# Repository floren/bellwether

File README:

# The Bellwether Mouse

This repo should contain everything you need to make a [Bellwether mouse](https://jfloren.net/bellwether.html).

## 3D-printed case

Inside the case/ subdirectory you'll find two FreeCAD files, "base" (the bottom part of the mouse) and "body" (the curved top which fits in your hand).

These should be printed in PLA. I've had good luck with my Prusa Mini. I strongly suggest using a raft when printing the body, and *not* using a raft for the base.

Check out the releases for pre-built STL files.

## PCB

The board was designed using KiCAD. If you use OSH Park, you should be able to just upload board/depraz_board.kicad_pcb directly on their site. For other PCB services, you may need to open KiCAD and export Gerber files etc.

## Circuit & BOM

You can check out the schematic in schematic.pdf

bom.csv is a circuit bill of materials. Most stuff should be available from parts companies in the US, but for the PMW3389 sensor you'll probably need to go to AliExpress (e.g. https://www.aliexpress.us/item/2251832705021246.html)

You'll also need 3 momentary pushbutton switches such as https://www.digikey.com/en/products/detail/5501M1BLKX/EG1701-ND/101654

Although you don't have to, I recommend using a DIP socket for the microcontroller in case you toast the microcontroller.

## Assembly

### Circuit assembly

In general it's all pretty straightforward but I strongly recommend installing the SMD level shifters first, all the rest of the components next, and then do the mouse sensor *last*.

### Doing the switches

I recommend gluing down the switches first. Gently pry off the button from each switch and set it aside. Then put a small dab of Gorilla Glue in the slot on the base, press the switch onto it, and make sure it's aligned straight. Use a clamp to hold the switch in place while the glue dries (I used something like https://www.amazon.com/Professional-Plastic-Backdrop-Photography-Improvement/dp/B08RXW32H4/). Once the glue is dry, make sure the switch is firmly seated and use an exacto knife to trim away any glue which oozed out, then press the button back onto the switch face.

Solder two wires onto each switch, on the normally-open pins. The wires should have Dupont pin connectors on the ends; I just took some jumper wires I had lying around (with a connector on each end) and cut them in half. See http://jfloren.net/content/bellwether/base2.jpg

### Physical assembly

You'll need the following parts to assemble the case:

* 8x M2x0.4mm heatserts: https://www.mcmaster.com/94459A120/
* 4x M2x0.4mm flathead screws (for the bottom): https://www.mcmaster.com/91294A003/
* 4x M2x0.4mm button head screws (to hold the board down): https://www.mcmaster.com/92095A451/

Additional stuff you'll want:

* A USB cable. Should be USB-A on one end, and a female pin header connector at the other. You can start with https://www.digikey.com/en/products/detail/assmann-wsw-components/A-USB20AM-OE-200BK28/10408422 and use https://www.amazon.com/Taiss-Ratcheting-Connector-Crimping-Terminal/dp/B0B11RLGDZ to crimp on a 4-pin header to the other end. You may be able to find these pre-made, e.g. https://www.amazon.com/dp/B07ZPT2NMT
* Friction tape (https://www.amazon.com/gp/product/B0000CBIAT) to wrap around the USB cable where it leaves the mouse. This appears to be what my original Depraz mouse used.
* Teflon tape to make skates for the bottom. I used https://www.amazon.com/gp/product/B01LZ44P6M and punched out pieces using https://www.amazon.com/gp/product/B00006IBK9

Use your soldering iron to install the heatserts flush in the corresponding holes of the case.

Position the lens on the bottom of the mouse sensor, then set the PCB on the 3d printed base. Use the button-head screws to hold down the PCB; don't overtighten!

Plug in the switches. Note that the headers on the board are labeled R, M, and L for right, middle, and left.

Plug the USB cable into the 4-pin USB header. Lay it across the board to where the cable hole in the case will go; mark this point and put a layer or two of friction tape on the cable there.

Gently slide the top of the case over the switches; there's a "right way" to do it, which takes a bit of gentle experimentation to find. Once you get the two pieces together, use flathead screws to hold them together.

Punch out four pieces of Teflon tape and stick them to the bottom for skates.

### Flashing the firmware

The firmware organization sucks, but I am not good enough at PIC programming to properly clean it up. PRs welcome.

Plug your PIC programmer into the PROGRAM header on the board.

Open MPLAB X IDE and load firmware/depraz/apps/usb/device/hid_mouse/firmware/low_pin_count_usb_development_kit_pic16f1459.x

I found that it worked when I set up the PICkit3 to provide power at 3.5V. Your other option is to plug in the USB cable before programming to power the device externally.

### Adding heft

You'll probably find that the mouse by itself is way too light. I hot-glued a bunch of lead fishing weights to the inside and it was much more pleasant.

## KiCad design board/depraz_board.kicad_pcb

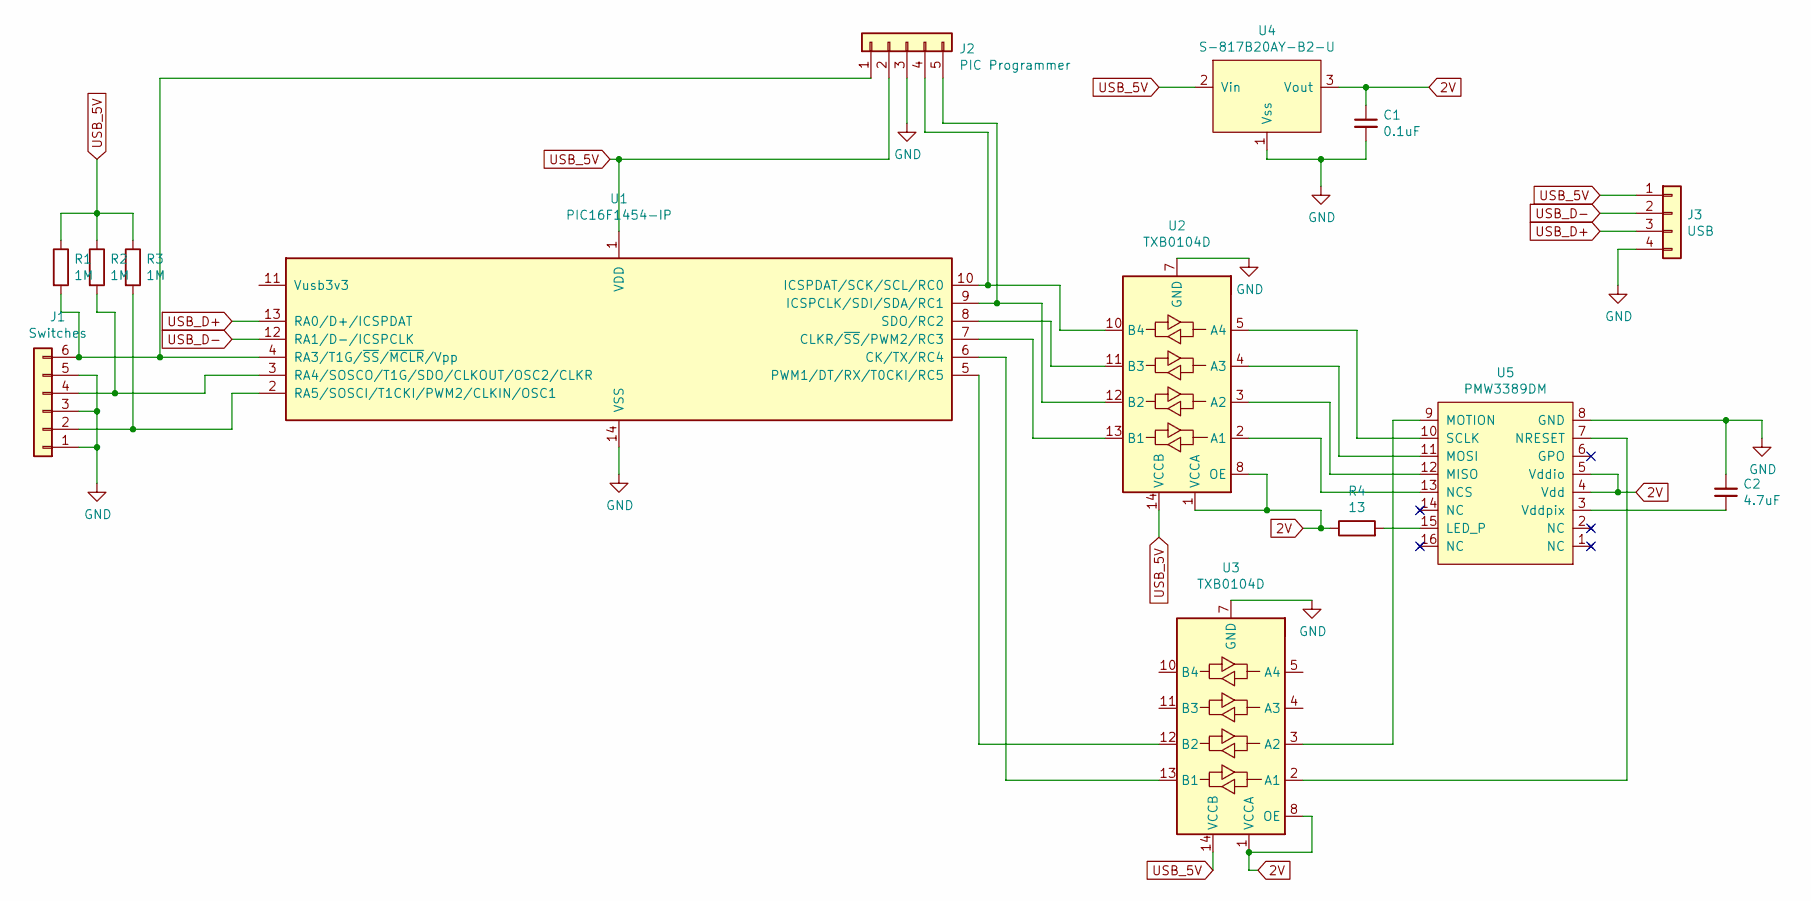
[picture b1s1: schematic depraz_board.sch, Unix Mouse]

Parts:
C1: 0.1uF; C_Disc_D8.0mm_W2.5mm_P5.00mm
C2: 4.7uF; C_Disc_D4.7mm_W2.5mm_P5.00mm
J1: Switches; PinHeader_1x06_P2.54mm_Vertical
J2: PIC Programmer; PinHeader_1x05_P2.54mm_Vertical
J3: USB; PinHeader_1x04_P2.54mm_Vertical
R1, R2, R3: 1M; R_Axial_DIN0207_L6.3mm_D2.5mm_P5.08mm_Vertical
R4: 13; R_Axial_DIN0207_L6.3mm_D2.5mm_P5.08mm_Vertical
U1: PIC16F1454-IP; DIP-14_W7.62mm
U2, U3: TXB0104D; SOIC-14_3.9x8.7mm_P1.27mm
U4: S-817B20AY-B2-U; TO-92L_Inline
U5: PMW3389DM; pmw3389

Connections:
2V: C1.1, R4.1, U2.1 (VCCA), U2.8 (OE), U3.1 (VCCA), U3.8 (OE), U4.3 (Vout), U5.4 (Vdd), U5.5 (Vddio)
GND: C1.2, C2.2, J1.1, J1.3, J1.5, J2.3, J3.4, U1.14 (VSS), U2.7 (GND), U3.7 (GND), U4.1 (Vss), U5.8 (GND)
unnamed: C2.1, U5.3 (Vddpix)
unnamed: J1.2, R3.2, U1.2 (RA5/SOSCI/T1CKI/PWM2/CLKIN/OSC1)
unnamed: J1.4, R2.2, U1.3 (RA4/SOSCO/T1G/SDO/CLKOUT/OSC2/CLKR)
unnamed: J1.6, J2.1, R1.2, U1.4 (RA3/T1G/~SS~/~MCLR~/Vpp)
unnamed: J2.4, U1.10 (ICSPDAT/SCK/SCL/RC0), U2.10 (B4)
unnamed: J2.5, U1.9 (ICSPCLK/SDI/SDA/RC1), U2.12 (B2)
unnamed: R4.2, U5.15 (LED_P)
unnamed: U1.5 (PWM1/DT/RX/T0CKI/RC5), U3.12 (B2)
unnamed: U1.6 (CK/TX/RC4), U3.13 (B1)
unnamed: U1.7 (CLKR/~SS~/PWM2/RC3), U2.13 (B1)
unnamed: U1.8 (SDO/RC2), U2.11 (B3)
unnamed: U2.2 (A1), U5.13 (NCS)
unnamed: U2.3 (A2), U5.12 (MISO)
unnamed: U2.4 (A3), U5.11 (MOSI)
unnamed: U2.5 (A4), U5.10 (SCLK)
unnamed: U3.2 (A1), U5.7 (NRESET)
unnamed: U3.3 (A2), U5.9 (MOTION)
USB_5V: J2.2, J3.1, R1.1, R2.1, R3.1, U1.1 (VDD), U2.14 (VCCB), U3.14 (VCCB), U4.2 (Vin)
USB_D+: J3.3, U1.13 (RA0/D+/ICSPDAT)
USB_D-: J3.2, U1.12 (RA1/D-/ICSPCLK)

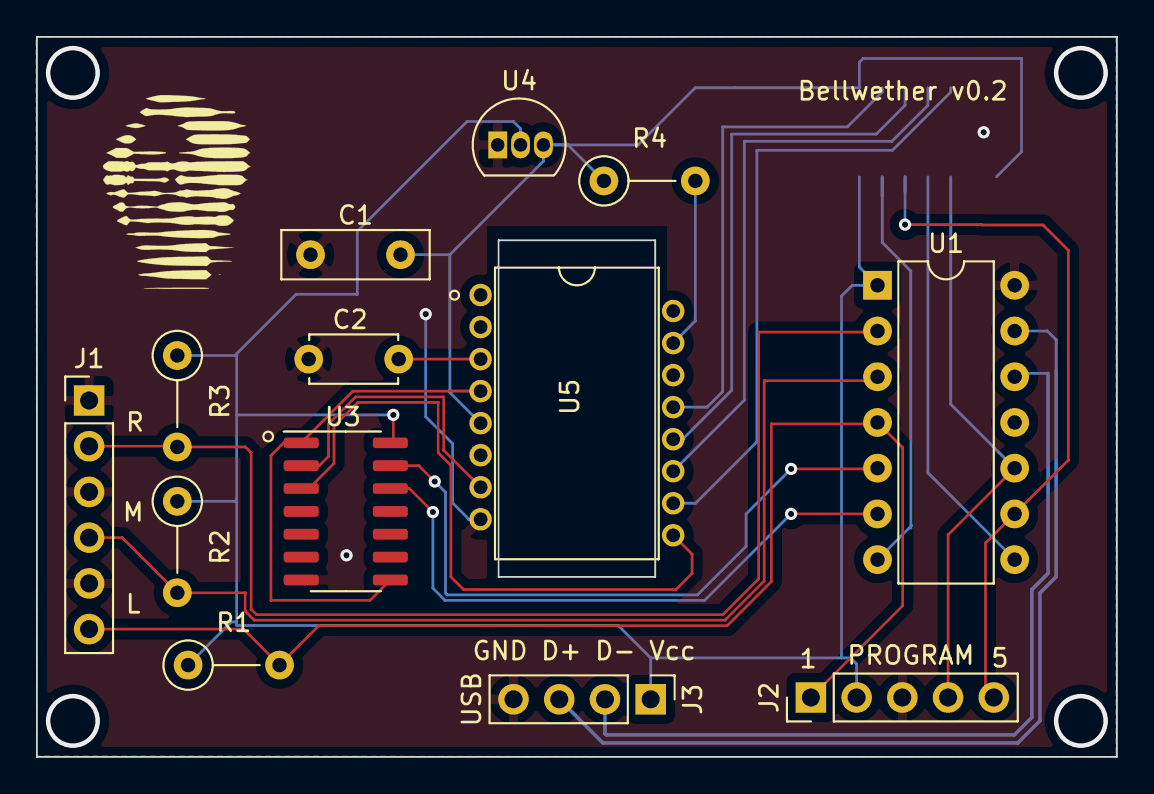
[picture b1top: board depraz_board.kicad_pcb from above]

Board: 2 copper layers, 60.0 x 40.0 mm, 14 parts (1 on the bottom side), 22 nets.

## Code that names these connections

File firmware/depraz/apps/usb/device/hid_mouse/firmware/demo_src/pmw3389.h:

/* Microchip Technology Inc. and its subsidiaries.  You may use this software 
 * and any derivatives exclusively with Microchip products. 
 * 
 * THIS SOFTWARE IS SUPPLIED BY MICROCHIP "AS IS".  NO WARRANTIES, WHETHER 
 * EXPRESS, IMPLIED OR STATUTORY, APPLY TO THIS SOFTWARE, INCLUDING ANY IMPLIED 
 * WARRANTIES OF NON-INFRINGEMENT, MERCHANTABILITY, AND FITNESS FOR A 
 * PARTICULAR PURPOSE, OR ITS INTERACTION WITH MICROCHIP PRODUCTS, COMBINATION 
 * WITH ANY OTHER PRODUCTS, OR USE IN ANY APPLICATION. 
 *
 * IN NO EVENT WILL MICROCHIP BE LIABLE FOR ANY INDIRECT, SPECIAL, PUNITIVE, 
 * INCIDENTAL OR CONSEQUENTIAL LOSS, DAMAGE, COST OR EXPENSE OF ANY KIND 
 * WHATSOEVER RELATED TO THE SOFTWARE, HOWEVER CAUSED, EVEN IF MICROCHIP HAS 
 * BEEN ADVISED OF THE POSSIBILITY OR THE DAMAGES ARE FORESEEABLE.  TO THE 
 * FULLEST EXTENT ALLOWED BY LAW, MICROCHIP'S TOTAL LIABILITY ON ALL CLAIMS 
 * IN ANY WAY RELATED TO THIS SOFTWARE WILL NOT EXCEED THE AMOUNT OF FEES, IF 
 * ANY, THAT YOU HAVE PAID DIRECTLY TO MICROCHIP FOR THIS SOFTWARE.
 *
 * MICROCHIP PROVIDES THIS SOFTWARE CONDITIONALLY UPON YOUR ACCEPTANCE OF THESE 
 * TERMS. 
 */

/* 
 * File:   
 * Author: 
 * Comments:
 * Revision history: 
 */

// This is a guard condition so that contents of this file are not included
// more than once.  
#ifndef PMW3389
#define	PMW3389

#include <xc.h> // include processor files - each processor file is guarded.  

// Pins on the PMW chip
#define NRESET RC4
#define NCS RC3
#define MOSI RC2
#define MISO RC1
#define SCK RC0

#define BUTTON_LEFT RA3
#define BUTTON_RIGHT RA5
#define BUTTON_MID RA4

#define Product_ID  0x00
#define Revision_ID 0x01
#define Motion  0x02
#define Delta_X_L 0x03
#define Delta_X_H 0x04
#define Delta_Y_L 0x05
#define Delta_Y_H 0x06
#define SQUAL 0x07
#define Raw_Data_Sum  0x08
#define Maximum_Raw_data  0x09
#define Minimum_Raw_data  0x0A
#define Shutter_Lower 0x0B
#define Shutter_Upper 0x0C
#define Control 0x0D
#define Resolution_L 0x0E
#define Resolution_H 0x0F
#define Config2 0x10
#define Angle_Tune  0x11
#define Frame_Capture 0x12
#define SROM_Enable 0x13
#define Run_Downshift 0x14
#define Rest1_Rate_Lower  0x15
#define Rest1_Rate_Upper  0x16
#define Rest1_Downshift 0x17
#define Rest2_Rate_Lower  0x18
#define Rest2_Rate_Upper  0x19
#define Rest2_Downshift 0x1A
#define Rest3_Rate_Lower  0x1B
#define Rest3_Rate_Upper  0x1C
#define Observation 0x24
#define Data_Out_Lower  0x25
#define Data_Out_Upper  0x26
#define Raw_Data_Dump 0x29
#define SROM_ID 0x2A
#define Min_SQ_Run  0x2B
#define Raw_Data_Threshold  0x2C
#define Config5 0x2F
#define Power_Up_Reset  0x3A
#define Shutdown  0x3B
#define Inverse_Product_ID  0x3F
#define LiftCutoff_Tune3  0x41
#define Angle_Snap  0x42
#define LiftCutoff_Tune1  0x4A
#define Motion_Burst  0x50
#define LiftCutoff_Tune_Timeout 0x58
#define LiftCutoff_Tune_Min_Length  0x5A
#define SROM_Load_Burst 0x62
#define Lift_Config 0x63
#define Raw_Data_Burst  0x64
#define LiftCutoff_Tune2  0x65

#endif	/* XC_HEADER_TEMPLATE_H */

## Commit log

2022-12-29 Import board and 3d models
2022-12-29 Add firmware, README, and licensing.
2022-12-29 tweak readme
